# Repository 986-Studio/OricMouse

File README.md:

# OricMouse
OricMouse, an Expansion card to add Mouse to your Orices! (1, Atmos and Telestrat)

You will find both the hardware and firmware of this project in this repository. 

OricMouse is an Open Source Hardware project.

Ready to order gerber can be found on OSHPark: https://oshpark.com/shared_projects/KOAZTB95

The correct license still need to be choosen, but please concidere it currently as something similar to the 4 clause BSD, share and use as wanted, but always tell from what your project is based, and who is the original author.
__Also if you make your own derived project, do not use the same name or a derived name.__ That mean that you can use the Oric name as I don't own this name, but don't use "OricMouse".

3D Rendering of the PCB:

Older revision of the PCB:

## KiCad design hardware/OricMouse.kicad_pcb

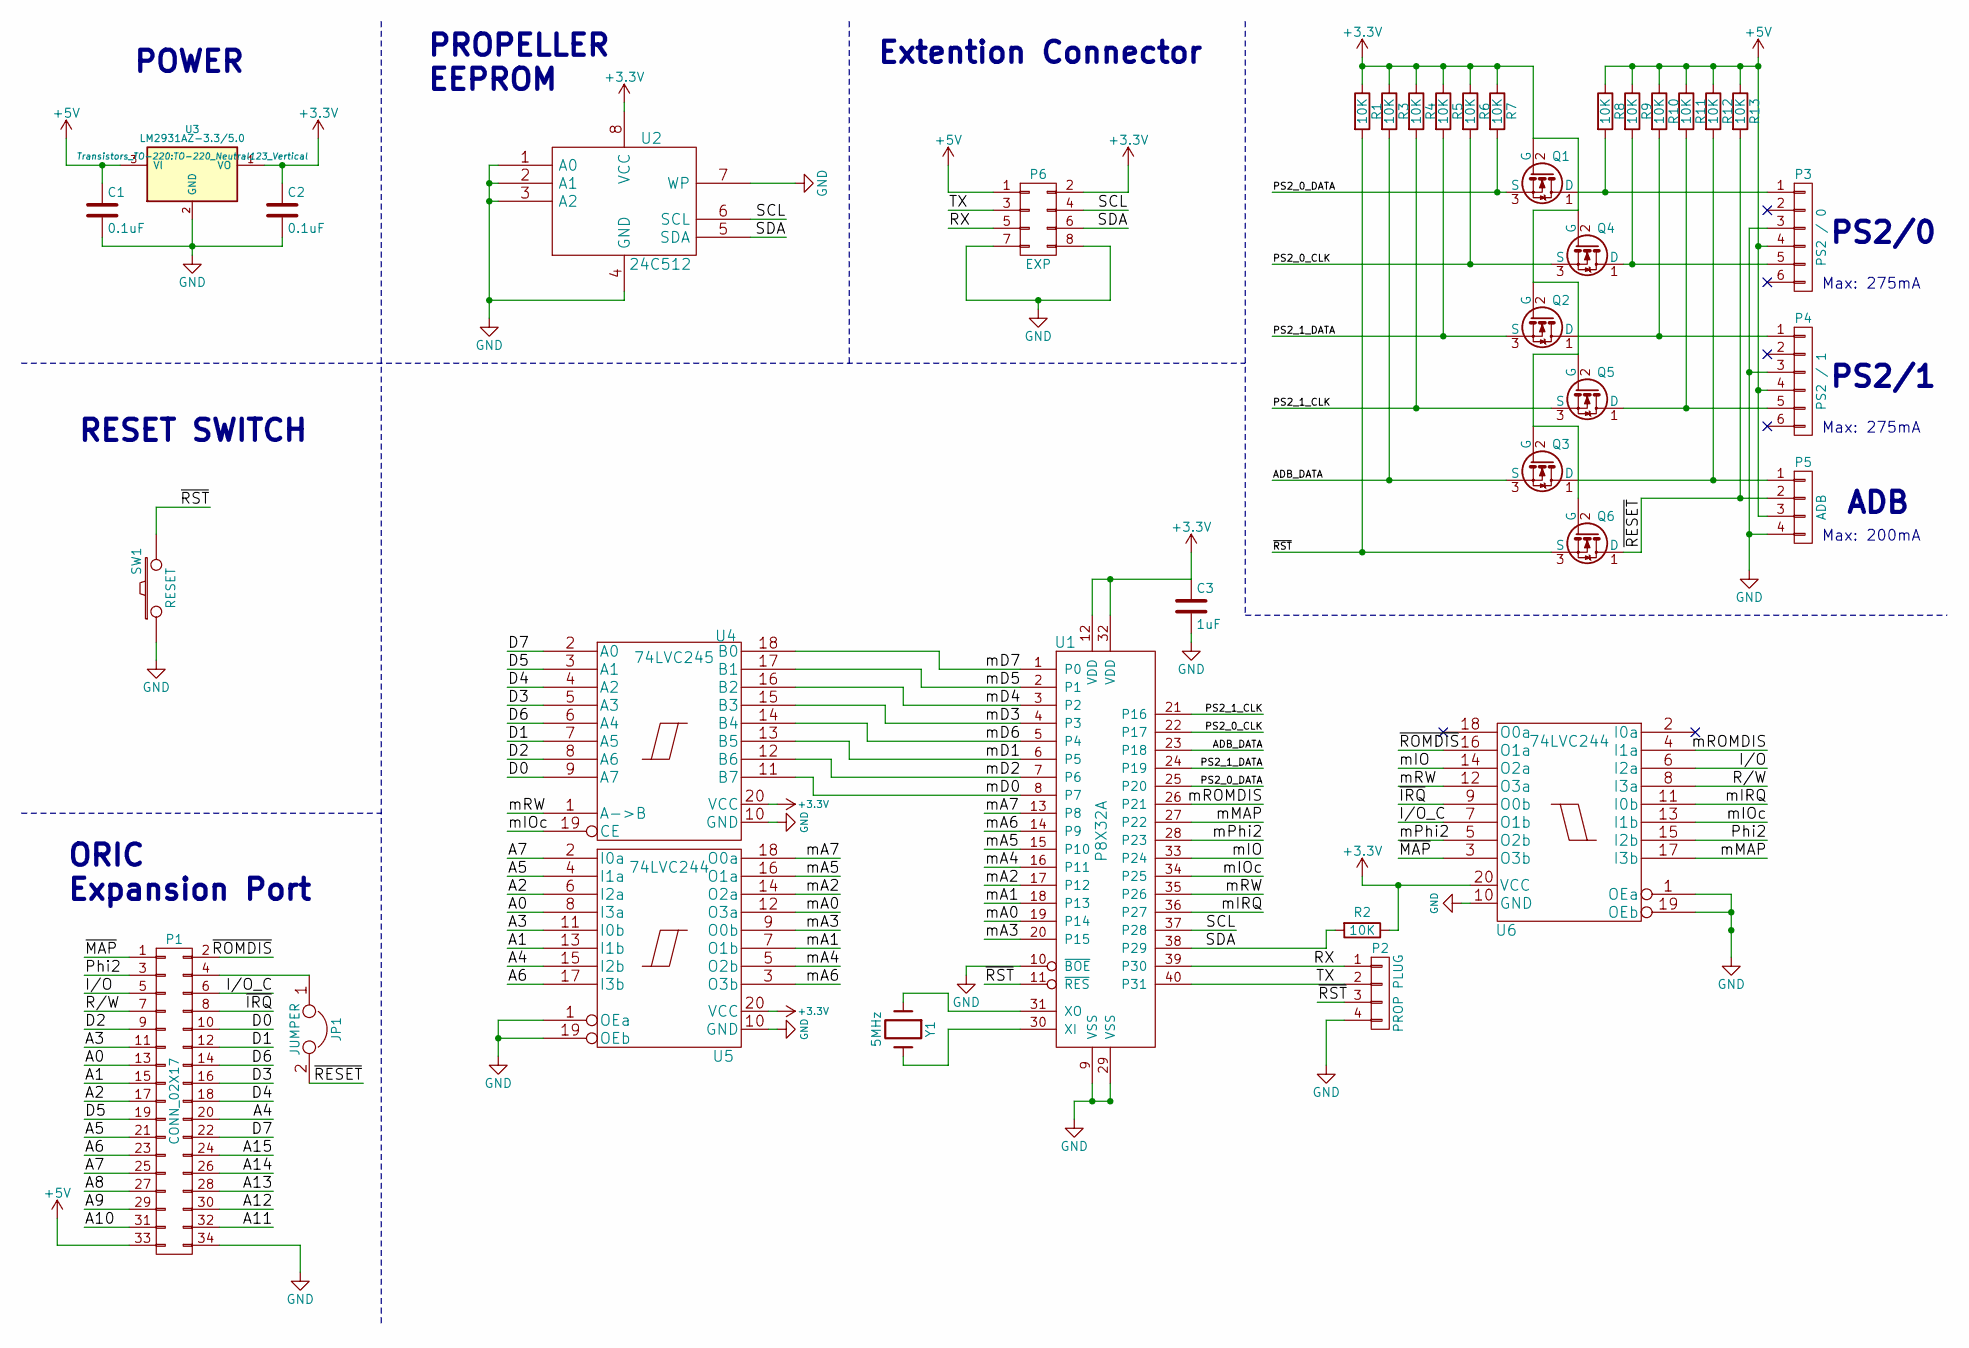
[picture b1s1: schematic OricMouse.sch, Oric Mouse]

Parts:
C1, C2: 0.1uF; C_Rect_L7_W2.5_P5
C3: 1uF; C_Rect_L7_W2.5_P5
JP1: JUMPER; Pin_Header_Straight_1x02
P1: CONN_02X17; Pin_Header_Straight_2x17
P2: PROP PLUG; Pin_Header_Straight_1x04
P3: PS2 / 0; MiniDIN6
P4: PS2 / 1; MiniDIN6
P5: ADB; MiniDIN4
P6: EXP; Pin_Header_Straight_2x04
Q1, Q2, Q3, Q4, Q5, Q6: BS170; TO-92_Inline_Narrow_Oval
R1, R2, R3, R4, R5, R6, R7, R8, R9, R10, R11, R12, R13: 10K; Resistor_Vertical_RM5mm
SW1: RESET; SW_PUSH_SMALL
U1: P8X32A; DIP-40_W15.24mm
U2: 24C512; DIP-8_W7.62mm
U3: LM2931AZ-3.3/5.0; TO-220_Neutral123_Vertical
U4: 74LVC245; DIP-20_W7.62mm
U5, U6: 74LVC244; DIP-20_W7.62mm
Y1: 5MHz; Crystal_HC50-U_Vertical

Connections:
+5V: C1.1, P1.33, P3.4, P4.4, P5.3, P6.1, R8.1, R9.1, R10.1, R11.1, R12.1, R13.1, U3.3 (VI)
/A0: P1.13, U5.8 (I3a)
/A1: P1.15, U5.13 (I1b)
/A2: P1.17, U5.6 (I2a)
/A3: P1.11, U5.11 (I0b)
/A4: P1.20, U5.15 (I2b)
/A5: P1.21, U5.4 (I1a)
/A6: P1.23, U5.17 (I3b)
/A7: P1.25, U5.2 (I0a)
/A8: P1.27
/A9: P1.29
/A10: P1.31
/A11: P1.32
/A12: P1.30
/A13: P1.28
/A14: P1.26
/A15: P1.24
/ADB_DATA: Q3.3 (S), R3.2, U1.23 (P18)
/D0: P1.10, U4.9 (A7)
/D1: P1.12, U4.7 (A5)
/D2: P1.9, U4.8 (A6)
/D3: P1.16, U4.5 (A3)
/D4: P1.18, U4.4 (A2)
/D5: P1.19, U4.3 (A1)
/D6: P1.14, U4.6 (A4)
/D7: P1.22, U4.2 (A0)
/I/O: P1.5, U6.6 (I2a)
/I/O_C: P1.6, U6.7 (O1b)
/PS2_0_CLK: Q4.3 (S), R6.2, U1.22 (P17)
/PS2_0_DATA: Q1.3 (S), R7.2, U1.25 (P20)
/PS2_1_CLK: Q5.3 (S), R4.2, U1.21 (P16)
/PS2_1_DATA: Q2.3 (S), R5.2, U1.24 (P19)
/Phi2: P1.3, U6.15 (I2b)
/R/W: P1.7, U6.8 (I3a)
/RX: P2.1, P6.5, U1.39 (P30)
/SCL: P6.4, U1.37 (P28), U2.6 (SCL); also elsewhere on the board
/SDA: P6.6, R2.2, U1.38 (P29), U2.5 (SDA)
/TX: P2.2, P6.3, U1.40 (P31)
/mA0: U1.19 (P14), U5.12 (O3a)
/mA1: U1.18 (P13), U5.7 (O1b)
/mA2: U1.17 (P12), U5.14 (O2a)
/mA3: U1.20 (P15), U5.9 (O0b)
/mA4: U1.16 (P11), U5.5 (O2b)
/mA5: U1.15 (P10), U5.16 (O1a)
/mA6: U1.14 (P9), U5.3 (O3b)
/mA7: U1.13 (P8), U5.18 (O0a)
/mD0: U1.8 (P7), U4.11 (B7)
/mD1: U1.6 (P5), U4.13 (B5)
/mD2: U1.7 (P6), U4.12 (B6)
/mD3: U1.4 (P3), U4.15 (B3)
/mD4: U1.3 (P2), U4.16 (B2)
/mD5: U1.2 (P1), U4.17 (B1)
/mD6: U1.5 (P4), U4.14 (B4)
/mD7: U1.1 (P0), U4.18 (B0)
/mIO: U1.33 (P24), U6.14 (O2a)
/mIOc: U1.34 (P25), U4.19 (CE), U6.13 (I1b)
/mIRQ: U1.36 (P27), U6.11 (I0b)
/mMAP: U1.27 (P22), U6.17 (I3b)
/mPhi2: U1.28 (P23), U6.5 (O2b)
/mROMDIS: U1.26 (P21), U6.4 (I1a)
/mRW: U1.35 (P26), U4.1 (A->B), U6.12 (O3a)
/~IRQ: P1.8, U6.9 (O0b)
/~MAP: P1.1, U6.3 (O3b)
/~RESET: JP1.2, P5.2, Q6.1 (D), R13.2
/~ROMDIS: P1.2, U6.16 (O1a)
/~RST: P2.3, Q6.3 (S), R1.2, SW1.2, U1.11 (~RES)
unnamed: JP1.1, P1.4
unnamed: P3.1, Q1.1 (D), R8.2
unnamed: P3.5, Q4.1 (D), R9.2
unnamed: P4.1, Q2.1 (D), R10.2
unnamed: P4.5, Q5.1 (D), R11.2
unnamed: P5.1, Q3.1 (D), R12.2
unnamed: U1.30 (XI), Y1.2
unnamed: U1.31 (XO), Y1.1

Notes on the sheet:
Max: 200mA
Max: 275mA
ORIC Expansion Port
POWER
RESET SWITCH
PROPELLER EEPROM
PS2/0
PS2/1
ADB
Extention Connector

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
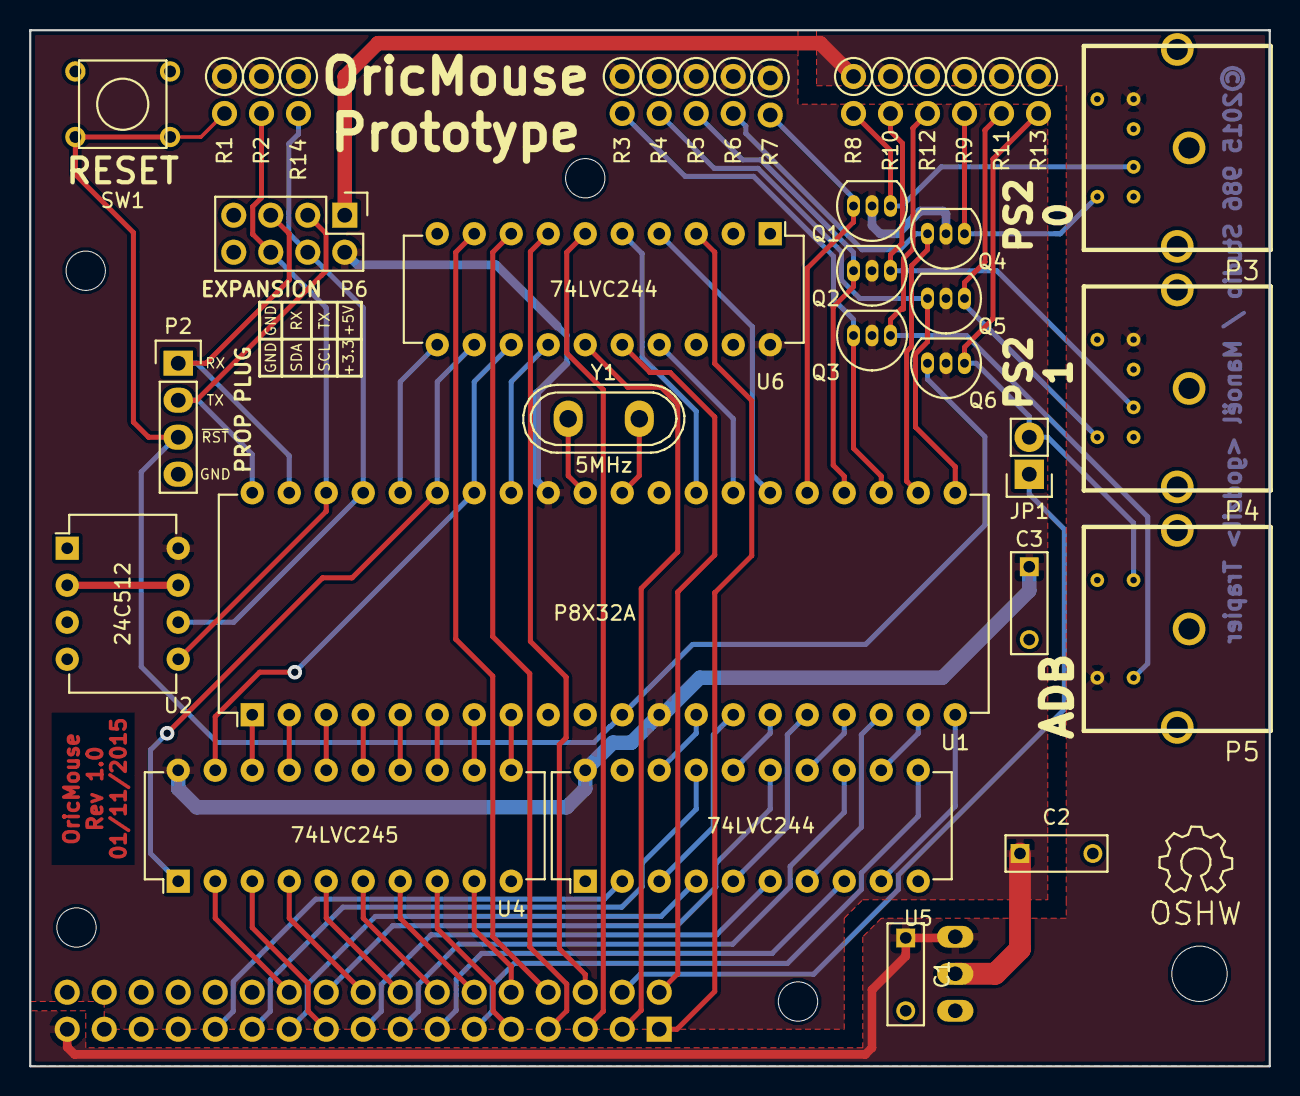
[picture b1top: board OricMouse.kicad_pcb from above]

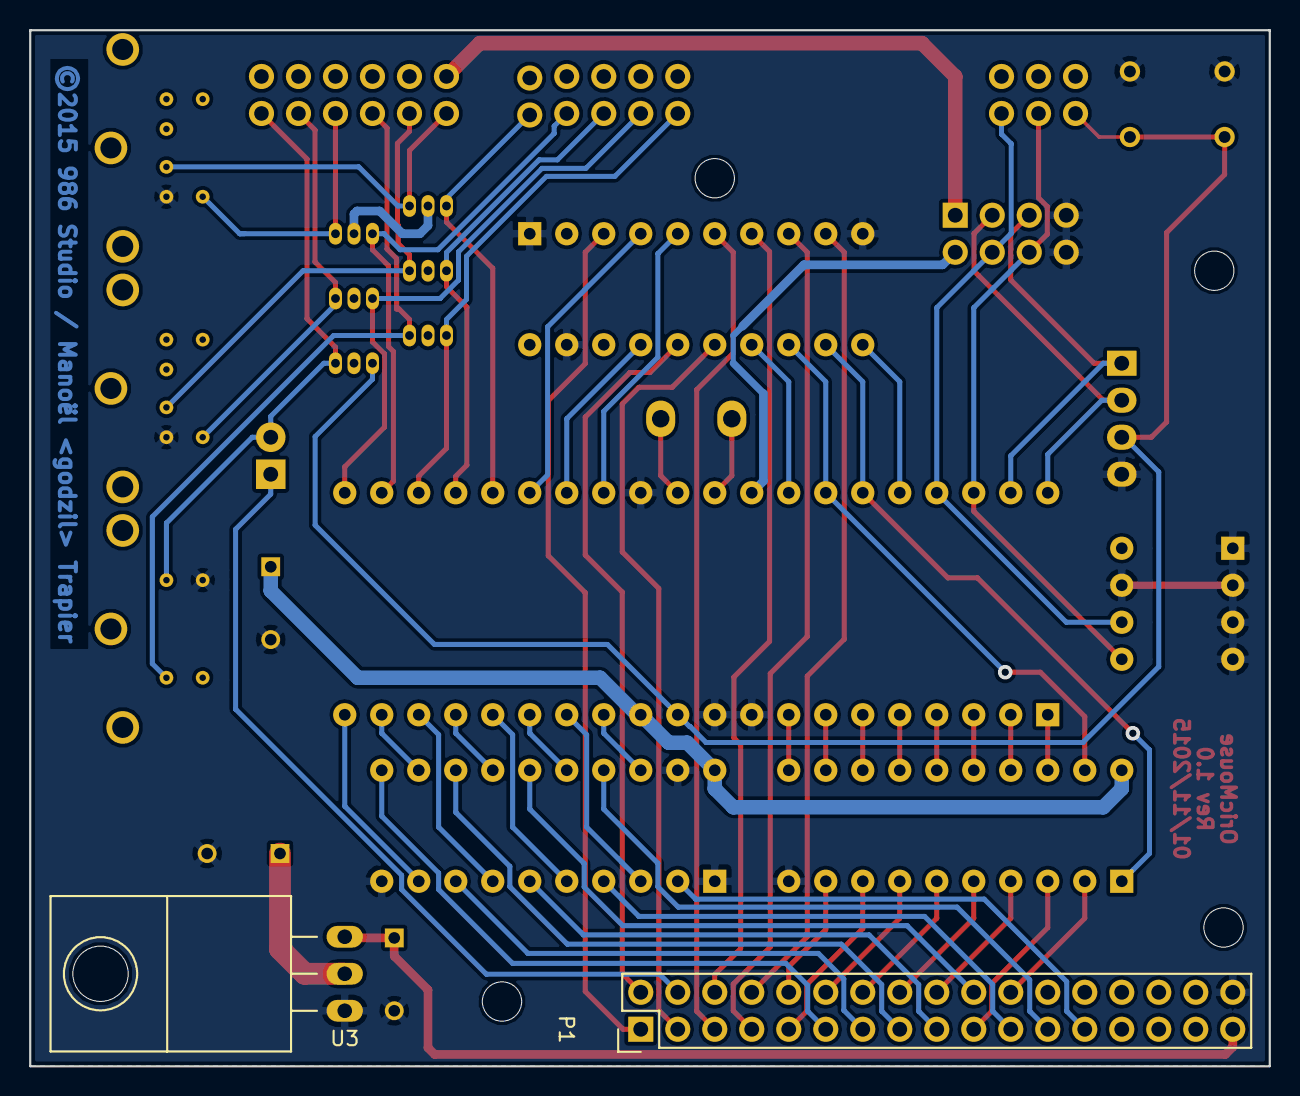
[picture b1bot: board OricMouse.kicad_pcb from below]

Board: 2 copper layers, 85.1 x 71.1 mm, 38 parts (2 on the bottom side), 68 nets.

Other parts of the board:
R14: 10K; Resistor_Vertical_RM5mm

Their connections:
/SCL: R14.2; also elsewhere on the board

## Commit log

2015-11-05 Add Rev 1.0 of the OricMouse PCB
2016-01-18 Add latest changes from 08/11/2015

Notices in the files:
hardware/OricMouse.kicad_pcb:
©2015 986 Studio / Manoël  Trapier
